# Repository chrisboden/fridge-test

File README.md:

# Fridge Temperature Tester

A KiCad project for testing fridge cooling element temperatures. This project contains the schematic and PCB design files for a temperature monitoring system that can be attached to the back of a fridge's cooling element to monitor its performance.

## Features

- High-precision temperature monitoring using DS18B20 digital temperature sensor
- Arduino Nano-based control system
- Operating range: -55°C to +125°C
- Accuracy: ±0.5°C
- USB interface for easy data logging and monitoring
- Compact PCB design (100mm x 50mm)

## Project Structure

- `Fridge_Temperature_Tester.sch` - KiCad schematic file
- `Fridge_Temperature_Tester.kicad_pcb` - PCB layout file

## Hardware Requirements

- Arduino Nano V3.x
- DS18B20 temperature sensor (waterproof version recommended)
- 4.7kΩ resistor
- USB cable for Arduino Nano
- Thermal paste or thermal adhesive tape

## Assembly Instructions

1. Fabricate the PCB using the provided KiCad files
2. Solder components according to the schematic:
   - Arduino Nano
   - DS18B20 temperature sensor
   - 4.7kΩ pull-up resistor
3. Apply thermal paste to the DS18B20 sensor
4. Attach the sensor to the fridge cooling element
5. Connect the Arduino Nano via USB

## Development

This project is developed using KiCad 7.x. To modify the project:

1. Install KiCad 7.0 or later
2. Open the `.sch` file in KiCad Schematic Editor
3. Open the `.kicad_pcb` file in KiCad PCB Editor

## License

Open source hardware - feel free to modify and use as needed.

## Author

Created by Chris Boden at Peregian Digital Hub

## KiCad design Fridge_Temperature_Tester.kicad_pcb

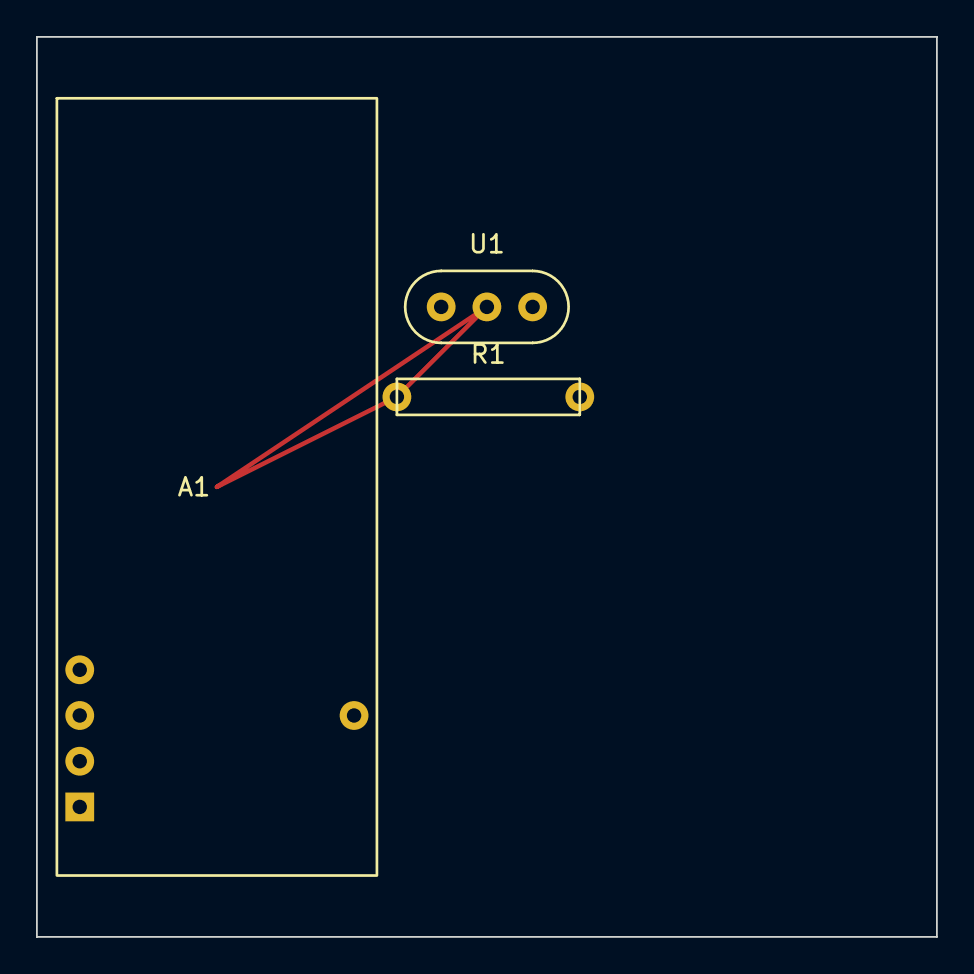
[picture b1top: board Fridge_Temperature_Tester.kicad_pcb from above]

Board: 2 copper layers, 50.0 x 50.0 mm, 3 parts (0 on the bottom side), 3 nets.

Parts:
A1: Arduino_Nano_v3.x; Arduino_Nano
R1: 4.7k; R_Axial_DIN0207
U1: DS18B20; TO-92_Inline

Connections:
+5V: A1.27, R1.1, U1.3
GND: A1.4, U1.1
TEMP_SENSOR: R1.2, U1.2

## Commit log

2025-03-10 Initial commit: Add KiCad project files
2025-03-10 Update README with comprehensive project information
2025-03-10 Update PCB layout with component placement and board outline
2025-03-10 Refine PCB design with improved component footprints and simplified board outline
